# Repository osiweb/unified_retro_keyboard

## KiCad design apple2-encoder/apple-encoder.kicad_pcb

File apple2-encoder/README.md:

# Apple II/II+ Encoder

This is a version of the ASCII interface wired up to be compatible with the
Apple II/Apple II+ keyboard matrix. This board was broken out as a separate PCB
from the Atmega2560-based interface board on which it was based, in order to
keep the "custom" connector customizable on that board.

This board is otherwise identical to rev 3.4 of the ATMega2560-based ASCII interface board, and shares the same firmware and features.

## Features
- Parallel or serial output
- Up to 8 configuration settings via an up-to-8 position DIP switch
- Apple 1, Apple 2, and SOL-20 compatible outputs. Other configurations can be
  supported by making a custom cable.
- Can decode arbitrary keyboards up 16 rows by 8 columns.
- Supports up to 3 keyboard LEDs
- Supports up to 3 "special" host outputs, such as RESET, SCREEN_CLEAR, BREAK, etc.
- Socket for custom connector

## Assembly Notes

- You may build this board as if it is a general purpose ASCII interface. In
   that case, you may want to avoid installing the 1x25 Apple2 keyboard header
   if it interferes with the target keyboard matrix. 
   
- This encoder is normally used with keyboards that have a diode per key.  For use 
with a key  matrix with no diodes (such as the Apple 2 key matrix), cut the PCB 
traces that short diodes D1-16, and install D1-16.

- If you ARE building this board as an Apple 2 encoder, then you may OMIT:

    - Sol-20 connector J5
    - Custom connector J7
    - D17,D18,D19 - These are used for the "classic" keyboard matrix.
    - D7,D8,D15,D16 - These are diodes for rows 12-15, which are not used.
    - The serial out connector J3 if you do not plan to use a serial output.
    - The I/O connector J4, as all the I/O lines are routed through the
       keyboard connector.
    - If you will be using the keyboard with only an Apple 1 or Apple 2, then
       you do not need to install both the Apple 2 connector (J1) AND the Apple
       1 connector (J2). You may install only the one you plan to use, and
       reduce the risk of plugging into the wrong socket (and possibly damaging
       the encoder).
    
1. Solder the surface-mount microcontroller first. Be sure to match pin 1 to the
   dot on the silk-screen layer.
1. Next, install the surface mount crystal, Y1.  The orientation is not important.
1. Next, solder in the resitor R1
1. Install all the capacitors. Be sure to separate out the two capacitors for the XTAL 
   circuit from the other capacitors, the rest of which are 0.1uF bypass capacitors.
1. Install the In-circuit Serial Programming (ISP) header, J6. (right-angle, 2x3
   0.100")
1. If you will be using the Apple 1 connector, install the DIP socket J1 (16-pin
   dip). If you plan to insert and remove the cable many times, a dual-wipe
   socket may be preferable to machine-pin, since it has a lower insertion
   force, and you will be less likely to bend pins. If you plan to insert the
   cable once and leave it forever, I suggest a machine-pin DIP socket.
1. If you will be using the Apple 2 connector, install the DIP socket J2 (16-pin
   dip).  The note for the Apple 1 connector selection applies here as well.

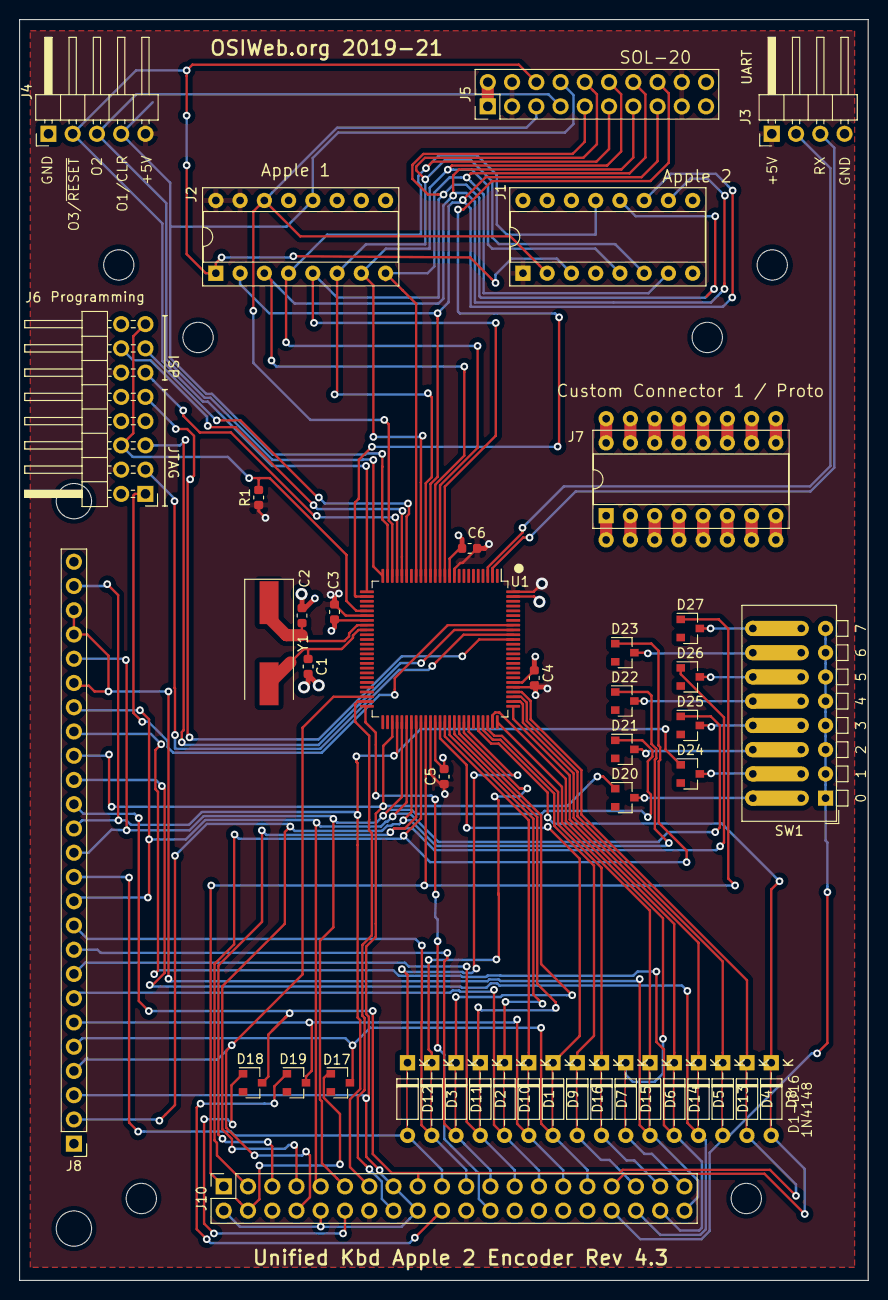
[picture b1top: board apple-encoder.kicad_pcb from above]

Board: 2 copper layers, 88.9 x 132.1 mm, 48 parts (0 on the bottom side), 80 nets.

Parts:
C1, C2: 36pf; C_0603_1608Metric
C3, C4, C5, C6: 0.1 uF; C_0603_1608Metric
D1, D2, D3, D4, D5, D6, D7, D8, D9, D10, D11, D12, D13, D14, D15, D16: 1N4148; D_DO-35_SOD27_P7.62mm_Horizontal_bypassed
D17, D18, D19, D20, D21, D22, D23, D24, D25, D26, D27: 1N4148; D_SOT-23_ANK
J1: Apple 2; DIP-16_W7.62mm_Socket
J2: Apple 1; DIP-16_W7.62mm_Socket
J3: UART; PinHeader_1x04_P2.54mm_Horizontal
J4: Outputs; PinHeader_1x05_P2.54mm_Horizontal
J5: SOL-20; SOL20-header-vertical
J6: Programming; PinHeader_2x08_P2.54mm_Horizontal
J7: Custom Connector 1 / Proto; DIP-16_W7.62mm_Proto
J8: Apple II Matrix; PinHeader_1x25_P2.54mm_Vertical
J10: Keyboard; kbd_header_and_mounting_holes
MH1, MH2: Apple II; MountingHole_3.7mm
R1: 10k; R_0603_1608Metric
SW1: Options; SW_DIP_SPSTx08_Piano_CTS_Series194-8MSTN_W7.62mm_P2.54mm
U1: ATmega2560-16AU; TQFP-100_14x14mm_P0.5mm
Y1: 16.000 MHz; Crystal_SMD_HC49-SD

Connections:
/Col0: D20.2, J8.3, J8.17, J10.2, J10.10, J10.15, J10.18, U1.53
/Col1: D24.2, J8.14, J8.24, J10.13, U1.54
/Col2: D21.2, J8.13, J8.21, J10.11, U1.55
/Col3: D25.2, J8.11, J8.19, J10.9, U1.56
/Col4: D22.2, J8.2, J10.7, U1.57
/Col5: D26.2, J10.5, U1.58
/Col6: D23.2, J10.3, U1.59
/Col7: D27.2, J10.1, U1.60
/D0: J1.12, J2.5, J5.5, U1.12
/D1: J1.13, J2.4, J5.6, U1.13
/D2: J1.10, J2.3, J5.7, U1.14
/D3: J1.11, J2.2, J5.8, U1.15
/D4: J1.6, J2.6, J5.15, U1.16
/D5: J1.5, J2.7, J5.16, U1.17
/D6: J1.7, J2.8, J5.17, U1.18
/D7: J5.18, U1.27
/LED1: J8.4, J10.8, U1.48
/LED2: J10.16, U1.49
/LED3: J10.24, U1.50
/MISO: J6.11, U1.22
/MOSI: J6.14, U1.21
/OUT1: J2.12, J4.4, J5.14, U1.24
/OUT2: J4.3, J5.4, U1.25
/OUT3: J1.3, J2.1, J4.2, J5.13, U1.26
/Row0: D9.2, D17.1, J8.5, J10.31
/Row1: D1.2, D19.1, J8.6, J10.29
/Row2: D10.2, J8.7, J10.27
/Row3: D2.2, J8.8, J10.25
/Row4: D11.2, J8.9, J10.23
/Row5: D3.2, J8.10, J10.21
/Row6: D12.2, J8.12, J10.19
/Row7: D4.2, D18.1, J8.15, J10.17
/Row8: D13.2, J10.34, SW1.1, SW1.2, SW1.3, SW1.4, SW1.5, SW1.6, SW1.7, SW1.8
/Row9: D5.2, J8.16, J10.36
/Row10: D14.2, J8.18, J10.38
/Row11: D6.2, J8.20, J8.22, J8.23, J10.40
/Row12: D15.2, J10.39
/Row13: D7.2, J10.37
/Row14: D16.2, J10.35
/Row15: D8.2, J10.33
/Rx: J3.3, U1.2
/SCK: J6.13, U1.20
/TCK: J6.1, U1.93
/TDI: J6.9, U1.90
/TDO: J6.3, U1.91
/TMS: J6.5, U1.92
/Tx: J3.2, U1.3
/~RESET: J6.6, J6.15, R1.2, U1.30
/~STROBE: J1.2, J2.14, J5.3, U1.23
GND: C1.2, C2.2, C3.2, C4.2, C5.2, C6.2, J1.8, J2.9, J3.4, J4.1, J5.1, J5.10, J5.11, J5.20, J6.2, J6.10, J6.16, U1.11, U1.32, U1.62, U1.81, U1.99
unnamed: C1.1, U1.34, Y1.2
unnamed: C2.1, U1.33, Y1.1
unnamed: D1.1, U1.64
unnamed: D2.1, U1.66
unnamed: D3.1, U1.68
unnamed: D4.1, U1.79
unnamed: D5.1, U1.77
unnamed: D6.1, U1.75
unnamed: D7.1, U1.73
unnamed: D8.1, U1.71
unnamed: D9.1, U1.63
unnamed: D10.1, U1.65
unnamed: D11.1, U1.67
unnamed: D12.1, U1.69
unnamed: D13.1, U1.78
unnamed: D14.1, U1.76
unnamed: D15.1, U1.74
unnamed: D16.1, U1.72
unnamed: D17.2, J10.4
unnamed: D18.2, J10.12
unnamed: D19.2, J10.20
unnamed: D20.1, SW1.16
unnamed: D21.1, SW1.14
unnamed: D22.1, SW1.12
unnamed: D23.1, SW1.10
unnamed: D24.1, SW1.15
unnamed: D25.1, SW1.13
unnamed: D26.1, SW1.11
unnamed: D27.1, SW1.9
VCC: C3.1, C4.1, C5.1, C6.1, J1.1, J2.15, J2.16, J3.1, J4.5, J5.2, J5.9, J5.12, J5.19, J6.4, J6.12, J10.6, J10.14, J10.22, R1.1, U1.10, U1.31, U1.61, U1.80, U1.100

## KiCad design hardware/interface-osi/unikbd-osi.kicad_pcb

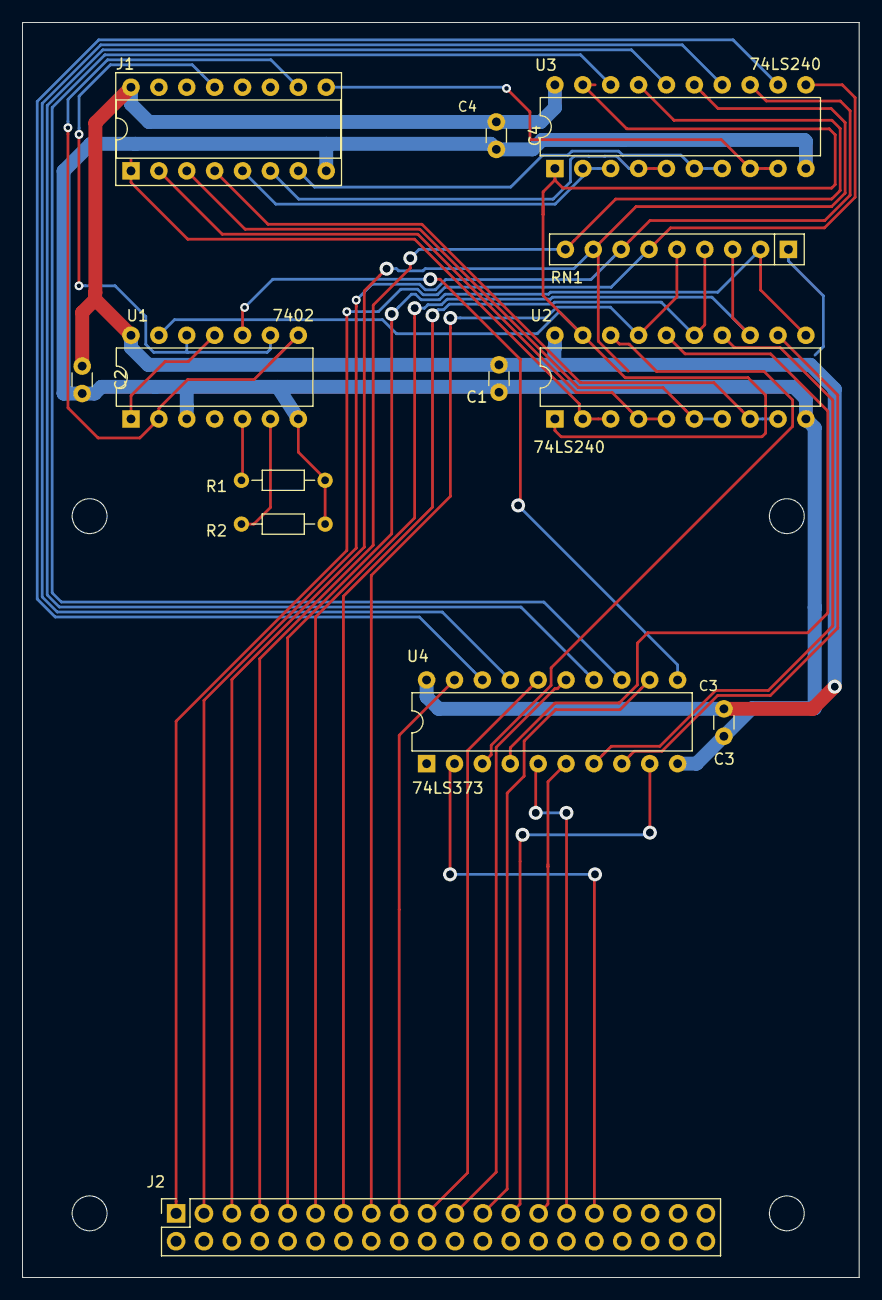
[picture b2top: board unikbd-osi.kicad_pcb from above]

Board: 2 copper layers, 76.2 x 114.3 mm, 13 parts (0 on the bottom side), 41 nets.

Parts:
C1, C2, C3: 0.1 uF; C_Disc_D3.0mm_W1.6mm_P2.50mm
C4: C; C_Disc_D3.0mm_W1.6mm_P2.50mm
J1: Conn_01x16; DIP-16_W7.62mm_Socket
J2: Conn_02x20_Odd_Even; PinSocket_2x20_P2.54mm_Vertical
R1, R2: 0 ohm; R_Axial_DIN0204_L3.6mm_D1.6mm_P7.62mm_Horizontal
RN1: 4.7k; R_Array_SIP9
U1: 7402; DIP-14_W7.62mm
U2, U3: 74LS240; DIP-20_W7.62mm
U4: 74LS373; DIP-20_W7.62mm

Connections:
+5V: C1.1, C2.1, C3.1, C4.1, J1.16, RN1.1, U1.14, U2.20, U3.20, U4.20
/Col0: J2.15, RN1.5, U2.17
/Col1: J2.13, RN1.4, U2.15
/Col2: J2.11, RN1.3, U2.13
/Col3: J2.9, RN1.2, U2.11
/Col4: J2.7, RN1.9, U3.17
/Col5: J2.5, RN1.8, U3.15
/Col6: J2.3, RN1.7, U3.13
/Col7: J2.1, RN1.6, U3.11
/D0: J1.1, U2.2, U2.3
/D1: J1.2, U2.4, U2.5
/D2: J1.3, U2.6, U2.7
/D3: J1.4, U2.8, U2.9
/D4: J1.5, U3.2, U3.3
/D5: J1.6, U3.4, U3.5
/D6: J1.7, U3.6, U3.7
/D7: J1.9, U3.8, U3.9
/R_~W: J1.10, U1.2, U1.8
/Row0: J2.31, U4.2
/Row1: J2.29, U4.5
/Row2: J2.27, U4.6
/Row3: J2.25, U4.9
/Row4: J2.23, U4.12
/Row5: J2.21, U4.15
/Row6: J2.19, U4.16
/Row7: J2.17, U4.19
/~KBE: J1.13, U1.9, U1.12
GND: C1.2, C2.2, C3.2, C4.2, J1.8, R1.2, R2.2, U1.3, U1.7, U2.10, U3.10, U4.1, U4.10
unnamed: R1.1, U1.5
unnamed: R2.1, U1.6
unnamed: U1.1, U1.11
unnamed: U1.10, U4.11
unnamed: U1.13, U2.1, U2.19, U3.1, U3.19
unnamed: U2.12, U4.8
unnamed: U2.14, U4.7
unnamed: U2.16, U4.4
unnamed: U2.18, U4.3
unnamed: U3.12, U4.18
unnamed: U3.14, U4.17
unnamed: U3.16, U4.14
unnamed: U3.18, U4.13
